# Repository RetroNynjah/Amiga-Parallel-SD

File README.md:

# Retroninja Amiga Parallel SD

<br/>

MicroSD SPI interface based on a design concept by [Niklas Ekström](https://github.com/niklasekstrom/amiga-par-to-spi-adapter)

It's quite useful for transferring files to and from the Amiga 500 and other Amiga models that doesn't have a PCMCIA interface or any other interface for mass storage devices.  
The difference from some previous designs is that this version is very small and fully integrated.  
It has a USB-C connector for power because the parallel port doesn't supply any power. It should be possible to take power from another port such as the floppy port or maybe even the joystick ports(?) if you have an adapter for that but I prefer to use an external power source.

A suitable Amiga driver for this device was developed by Niklas Ekström. The source code and a compiled driver can be found in his [release archive](https://github.com/niklasekstrom/amiga-par-to-spi-adapter/releases).

Revision 3 of this board is using a different connection of the activity LED compared to earlier designs and revisions so rev 3 boards needs a different firmware for the LED to work. Jörgen Bilander has created a suitable firmware for this. The source code is available in [his repository](https://github.com/jbilander/amiga-par-to-spi-adapter). I have precompiled hex files for all variants in the [firmware](rev3/firmware) folder.

I have designed a 3D-printable enclosure which can be found at https://www.thingiverse.com/thing:6799759/files

## Installation
You need the spisd.device driver in Devs: and the [fat95 DOS handler](https://aminet.net/package/disk/misc/fat95) in L: and you need a suitable mount file, either in Devs:DOSDrivers for auto-mounting or in a convenient location for mounting on demand.  
For WB1.3/2.0 installations you need to add the device settings to the file Devs:MountList instead. You also need to run the mount command to mount the device using the settings in your mount list. Type `mount SD0:` to mount the device or add that to your startup-sequence to have it available at all times.  
I have a suitable mount file (SD0) and MountList settings in the [amiga](amiga/) folder in this Github repository.

> [!CAUTION]
> Do **NOT** insert or remove the device while the computer is running.

## BOM
|Parts|Device|Value|Qty|Comment
|-----|-----|-----|-----|-----|
|C1, C2, C6, C8|Ceramic capacitor 0805|100nF|4||
|C5, C7|Tantalum capacitor 0805|10uF/10V|2||
|C3, C4|Ceramic capacitor 0805|30pF|2||
|R1, R7|Resistor 0805|10kΩ|2||
|R2, R3|Resistor 0805|5.1kΩ|2||
|R4|Resistor 0805|100R|1|Rev 2 only|
|R5|Resistor 0805|100kΩ|1|Rev 2 only|
|R6|Resistor 0805|560R|1||
|IC1|MCU 32-TQFP|ATmega328|1||
|IC2|3.3V regulator SOT-223|1117-3.3|1||
|IC3|Quad bus buffer|74LVC125A|1||
|Q1|P-channel MOSFET SOT-23|BSS84|1|Rev 2 only|
|D1|LED|3mm LED|1||
|Y1|16MHz Crystal|ECS-160-20-3X-TR|1||
|J1|D-Sub Male|25-pin|1||
|J2|8-pin push-push MicroSD connector|Würth 693071020811|1||
|J3|USB-C Connector|Molex 2171750001|1||
|J4|ICSP-6 header (optional)|2x3-pin|1||

#### Some notes about the parts in the BOM
The crystal capacitors C3 and C4 should ideally match your crystal but in general it will work just fine with any capacitors around 20-30pF.

The voltage regulator is a 3.3V 1117 type regulator. These are available from plenty of manufacturers and the exact part numbers vary. Use whatever you can find.

The D-sub can have either through hole pins or solder cups. I prefer solder cups as they provide a tighter fit over the PCB edge.

The ICSP header is a regular 2x3 pin-header. I usually leave it out and use a 2x3 pogo pin adapter for uploading firmware. It's also posible to just stick a connector into the slots and push it gently sideways to make contact while uploading the firmware.

The original design was based around an ATmgea328-based Arduino Nano module but with this board a wide range of ATmega328/168/88/48 MCU:s can be used, at least with the current firmware version. Use whatever you can lay your hands on for the day. ATmega48/88/168/328 A/P/PA/PB should all work. ATmega328P is recommended.

A compatible MicroSD connector can be found on AliExpress at a much better price than the Würth connector: https://www.aliexpress.com/item/32802051702.html

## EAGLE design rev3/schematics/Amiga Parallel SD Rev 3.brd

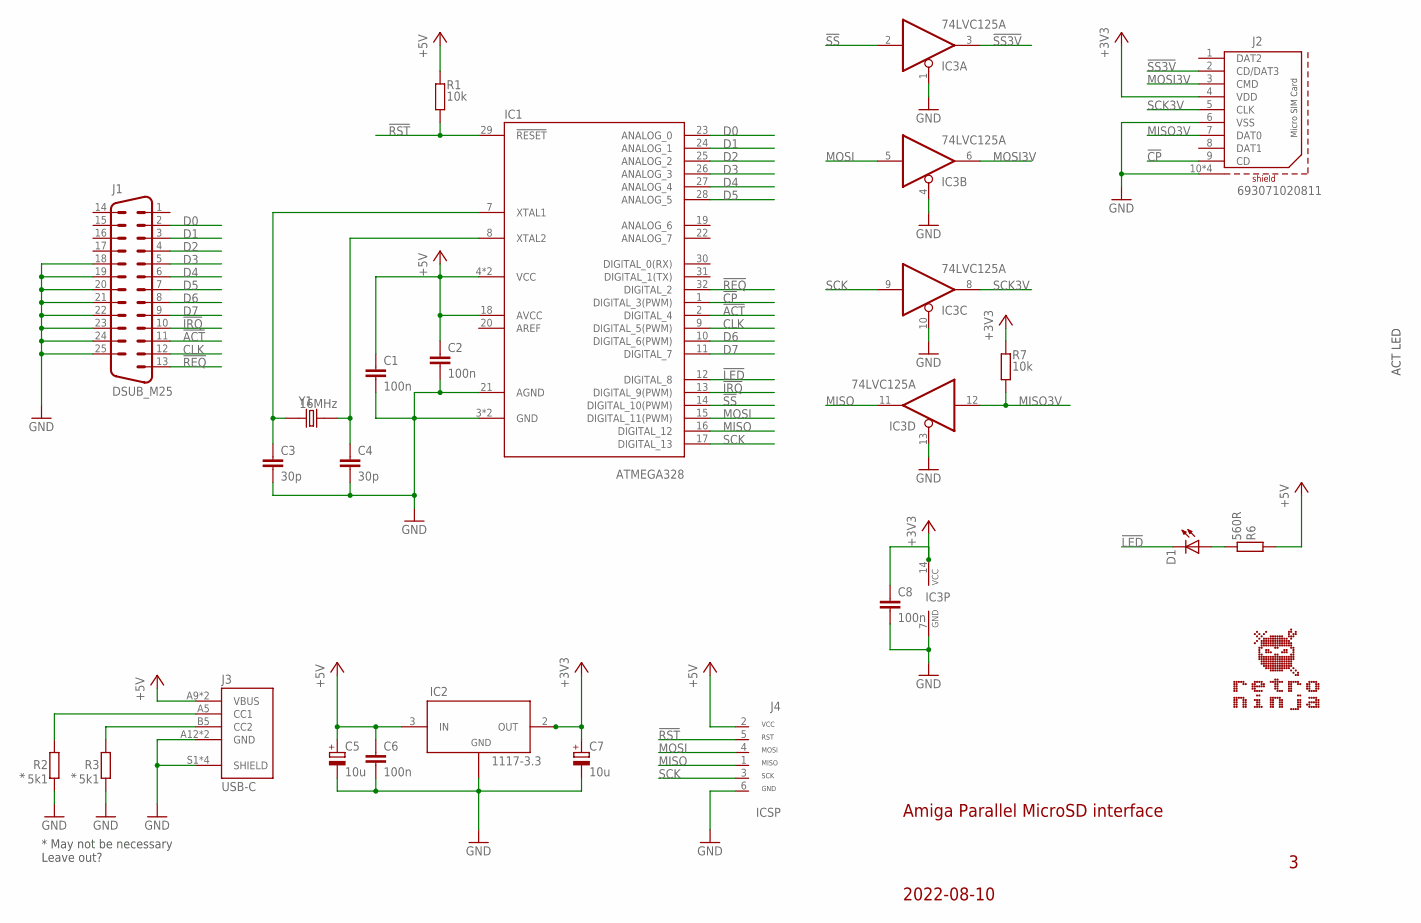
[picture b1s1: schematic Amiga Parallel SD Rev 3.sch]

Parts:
C1, C2, C6, C8: 100n; C0805
C3, C4: 30p; C0805
C5, C7: 10u; TANTALUM_0805
D1: LED_3MM_GREEN; LED3MM_GREEN
IC1: ATMEGA328; TQFP-32
IC2: 1117-3.3; SOT-223
IC3: 74LVC125A; SO14
J1: DSUB_M25; DSUB_M25D
J2: 693071020811
J3: USB-C; MOLEX_2171750001
J4: ICSP; HEADER_2X3_ALT
R1, R7: 10k; R0805
R2, R3: 5k1; R0805
R6: 560R; R0805
Y1: 16MHz; CRYSTAL_SMD-2_7X4X2.3

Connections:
!ACT: IC1.2 (DIGITAL_4), J1.11
!CP: IC1.1 (DIGITAL_3(PWM)), J2.9 (CD)
!IRQ: IC1.13 (DIGITAL_9(PWM)), J1.10
!LED: D1.K (C), IC1.12 (DIGITAL_8)
!REQ: IC1.32 (DIGITAL_2), J1.13
!RST: IC1.29 (!RESET), J4.5 (RST), R1.2
!SS: IC1.14 (DIGITAL_10(PWM)), IC3.2 (I)
!SS3V: IC3.3 (O), J2.2 (CD/DAT3)
+3V3: C7.+, C8.1, IC2.2 (OUT), IC2.4, IC3.14 (VCC), J2.4 (VDD), R7.1
+5V: C1.1, C2.1, C5.+, C6.1, IC1.4 (VCC), IC1.6 (VCC), IC1.18 (AVCC), IC2.3 (IN), J3.A9 (VBUS), J3.B9 (VBUS), J4.2 (VCC), R1.1, R6.2
A5: J3.A5 (CC1), R2.2
B5: J3.B5 (CC2), R3.2
CLK: IC1.9 (DIGITAL_5(PWM)), J1.12
D0: IC1.23 (ANALOG_0), J1.2
D1: IC1.24 (ANALOG_1), J1.3
D2: IC1.25 (ANALOG_2), J1.4
D3: IC1.26 (ANALOG_3), J1.5
D4: IC1.27 (ANALOG_4), J1.6
D5: IC1.28 (ANALOG_5), J1.7
D6: IC1.10 (DIGITAL_6(PWM)), J1.8
D7: IC1.11 (DIGITAL_7), J1.9
GND: C1.2, C2.2, C3.2, C4.2, C5.-, C6.2, C7.-, C8.2, IC1.3 (GND), IC1.5 (GND), IC1.21 (AGND), IC2.1 (ADJ/GND), IC3.1 (OE), IC3.4 (OE), IC3.7 (GND), IC3.10 (OE), IC3.13 (OE), J1.18, J1.19, J1.20, J1.21, J1.22, J1.23, J1.24, J1.25, J2.6 (VSS), J2.10 (SHIELD), J2.11 (SHIELD), J2.12 (SHIELD), J2.13 (SHIELD), J3.A12 (GND), J3.B12 (GND), J3.S1 (SHIELD), J3.S2 (SHIELD), J3.S3 (SHIELD), J3.S4 (SHIELD), J4.6 (GND), R2.1, R3.1
MISO: IC1.16 (DIGITAL_12), IC3.11 (O), J4.1 (MISO)
MISO3V: IC3.12 (I), J2.7 (DAT0), R7.2
MOSI: IC1.15 (DIGITAL_11(PWM)), IC3.5 (I), J4.4 (MOSI)
MOSI3V: IC3.6 (O), J2.3 (CMD)
unnamed: D1.A, R6.1
unnamed: C4.1, IC1.8 (XTAL2), Y1.1
unnamed: C3.1, IC1.7 (XTAL1), Y1.2
SCK: IC1.17 (DIGITAL_13), IC3.9 (I), J4.3 (SCK)
SCK3V: IC3.8 (O), J2.5 (CLK)

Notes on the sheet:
* May not be necessary Leave out?
ACT LED
Amiga Parallel MicroSD interface
2022-08-10

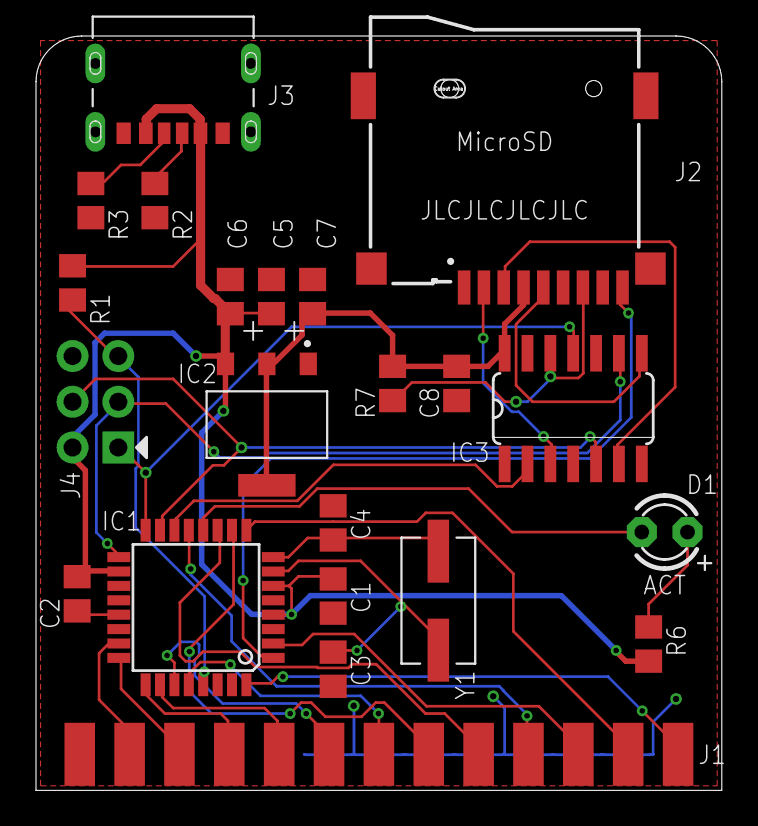
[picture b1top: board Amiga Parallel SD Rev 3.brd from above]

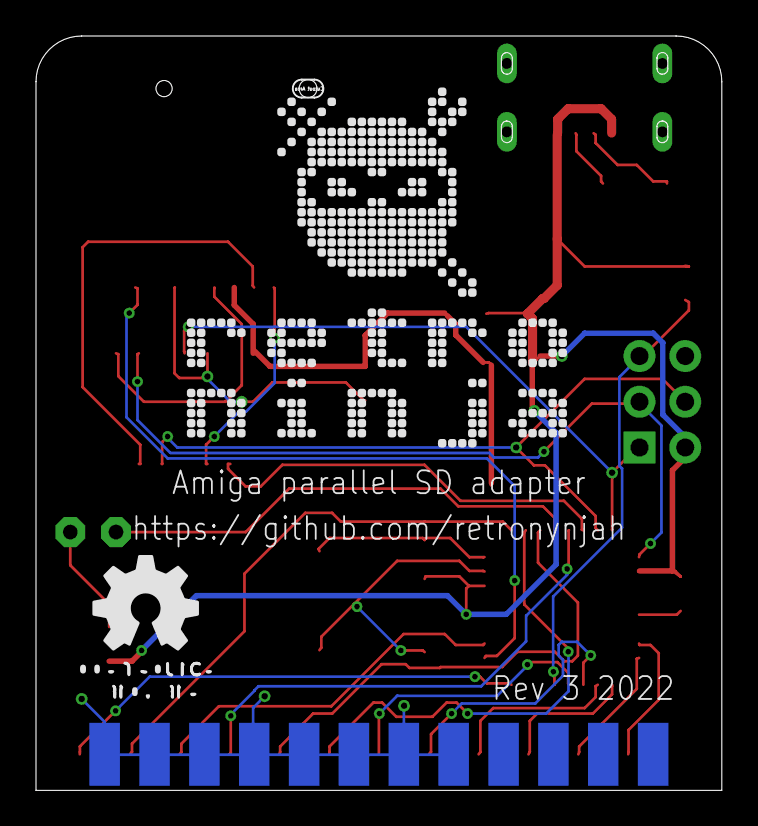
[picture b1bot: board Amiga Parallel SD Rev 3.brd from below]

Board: 2 copper layers, 38.0 x 41.8 mm, 24 parts (2 on the bottom side), 31 nets.

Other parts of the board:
U$1: RETRONINJA_20MM
U$2: OSHW_8MM

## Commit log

2022-03-14 Upload
2022-03-16 Uploading mount file
2022-03-17 Added firmware images and tools
2024-10-16 Update README.md
    Updated software release link
    Added link for 3D-printable enclosure
2025-01-11 Enclosure added
2025-03-09 Revision 3 published
    The previously unreleased rev 3 is finally published

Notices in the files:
parts and their libraries:
Wurth_Connectors_WR-CRD: Copyright: Würth Elektronik
